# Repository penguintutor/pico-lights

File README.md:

# pico-lights
Raspberry Pi Pico LED Light Controller

Controls LED low-voltage lighting using a Raspberry Pi Pico and the Pico Lights Board.

# Code

There are three different programs included. The basic program is simple-lights.py which can be run on any Raspberry Pi Pico, with an appropriate external circuit. 
For a web based version you will need a Raspberry Pi Pico W with the web-lights.py program. Or the web-lights-twinkle.py also adds support for flashing or twinkling lights, ideal for Christmas. 

For the network versions you also need a file named secrets.py with details of your SSID and PASSWORD. The example below shows the formatting for the secrets.py file.

    SSID="NetworkSSID"
    PASSWORD="WiFiPassword"

For the web versions you should also upload the public folder and the file url_handler.py. These can be transferred using the Thonny editor.

## Running on startup

For the code to run automatically on start-up save the appropriate file (simple-lights.py, web-lights.py or web-lights-twinkle.py) to your Pico as main.py.

# Printed Circuit Board

The design files for the PCB are included in the folder pcb-design. This includes a zip of the gerber files which are exported for JLCPCB. Other manufacturers may need the files to be in a different format.

For further details of the printed circuit board see [PenguinTutor Pico Lights Board](https://www.penguintutor.com/projects/pico-lights)

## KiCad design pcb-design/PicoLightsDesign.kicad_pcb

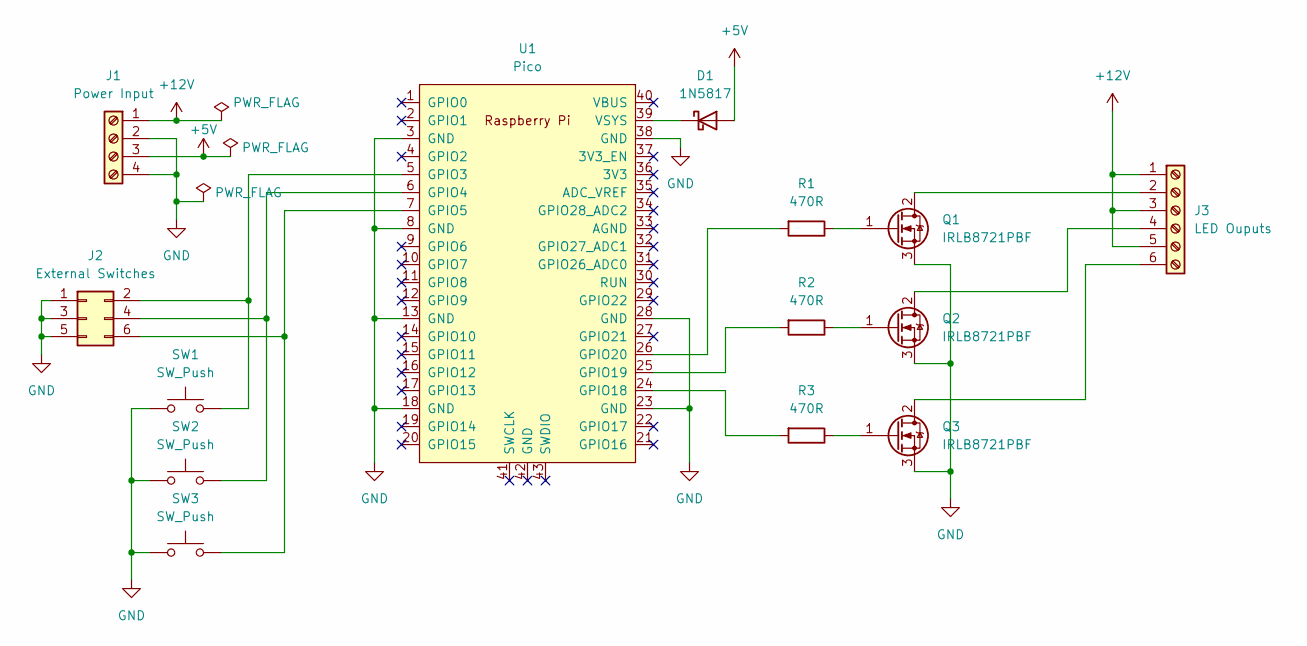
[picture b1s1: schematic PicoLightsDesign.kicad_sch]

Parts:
D1: 1N5817; D_DO-41_SOD81_P10.16mm_Horizontal
J1: Power Input; TerminalBlock_Phoenix_MKDS-1,5-4_1x04_P5.00mm_Horizontal
J2: External Switches; PinHeader_2x03_P2.54mm_Vertical
J3: LED Ouputs; TerminalBlock_Phoenix_MKDS-1,5-6_1x06_P5.00mm_Horizontal
Q1, Q2, Q3: IRLB8721PBF; TO-220-3_Vertical
R1, R2, R3: 470R; R_Axial_DIN0411_L9.9mm_D3.6mm_P15.24mm_Horizontal
SW1, SW2, SW3: SW_Push; SW_PUSH-12mm
U1: Pico; RPi_Pico_SMD_TH

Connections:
+5V: D1.2 (A), J1.3
+12V: J1.1, J3.1, J3.3, J3.5
GND: J1.2, J1.4, J2.1, J2.3, J2.5, Q1.3 (S), Q2.3 (S), Q3.3 (S), SW1.1, SW2.1, SW3.1, U1.3 (GND), U1.8 (GND), U1.13 (GND), U1.18 (GND), U1.23 (GND), U1.28 (GND), U1.38 (GND)
unnamed: D1.1 (K), U1.39 (VSYS)
unnamed: J2.2, SW1.2, U1.5 (GPIO3)
unnamed: J2.4, SW2.2, U1.6 (GPIO4)
unnamed: J2.6, SW3.2, U1.7 (GPIO5)
unnamed: J3.2, Q1.2 (D)
unnamed: J3.4, Q2.2 (D)
unnamed: J3.6, Q3.2 (D)
unnamed: Q1.1 (G), R1.1
unnamed: Q2.1 (G), R2.1
unnamed: Q3.1 (G), R3.1
unnamed: R1.2, U1.26 (GPIO20)
unnamed: R2.2, U1.25 (GPIO19)
unnamed: R3.2, U1.24 (GPIO18)

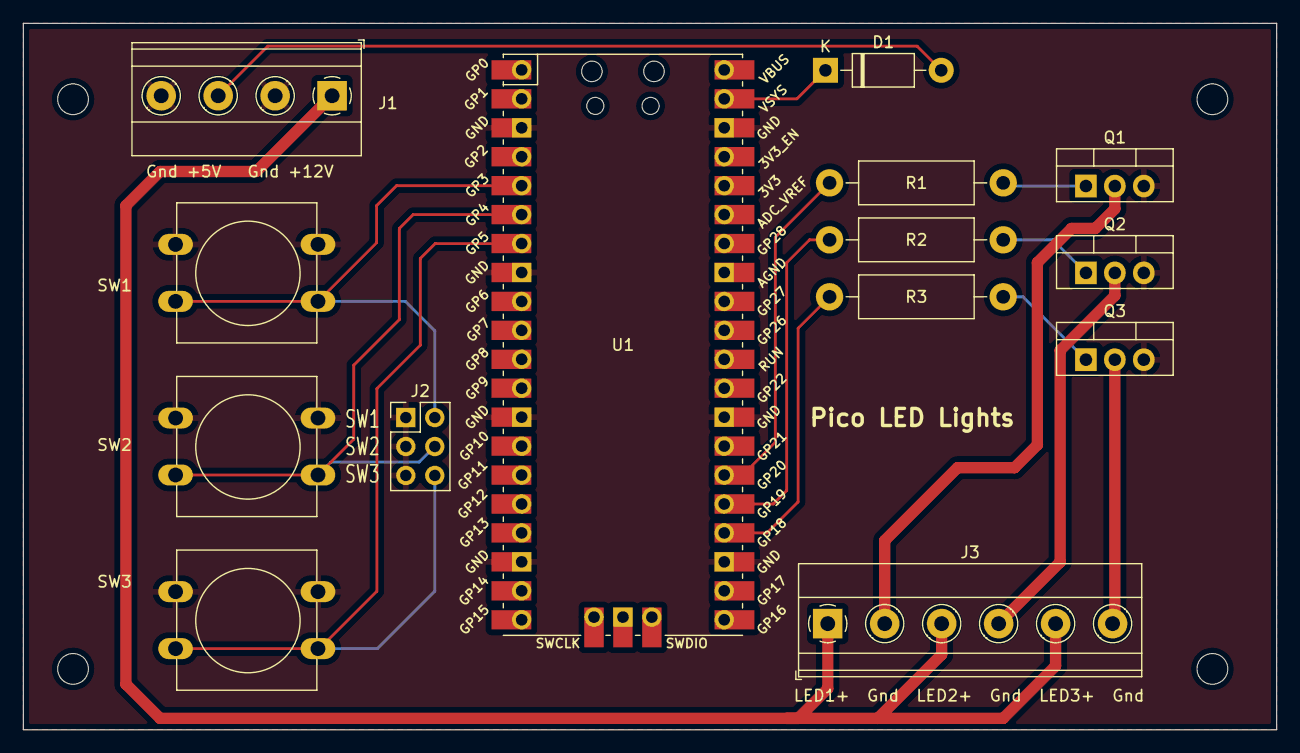
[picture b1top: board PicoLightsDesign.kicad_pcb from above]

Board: 2 copper layers, 110.0 x 62.0 mm, 14 parts (0 on the bottom side), 16 nets.

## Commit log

2023-08-20 Simple example to toggle ouputs with switches
2023-08-20 Add web version
2023-09-28 Add install instructions to README.md
2023-09-28 Fix markup in README.md
2023-10-01 Add KiCAD PCB Design
2023-10-01 Remove cache file
2025-12-02 Add web-lights-twinkle.py with extra flash options
2025-12-05 Improved twinkle sequence
